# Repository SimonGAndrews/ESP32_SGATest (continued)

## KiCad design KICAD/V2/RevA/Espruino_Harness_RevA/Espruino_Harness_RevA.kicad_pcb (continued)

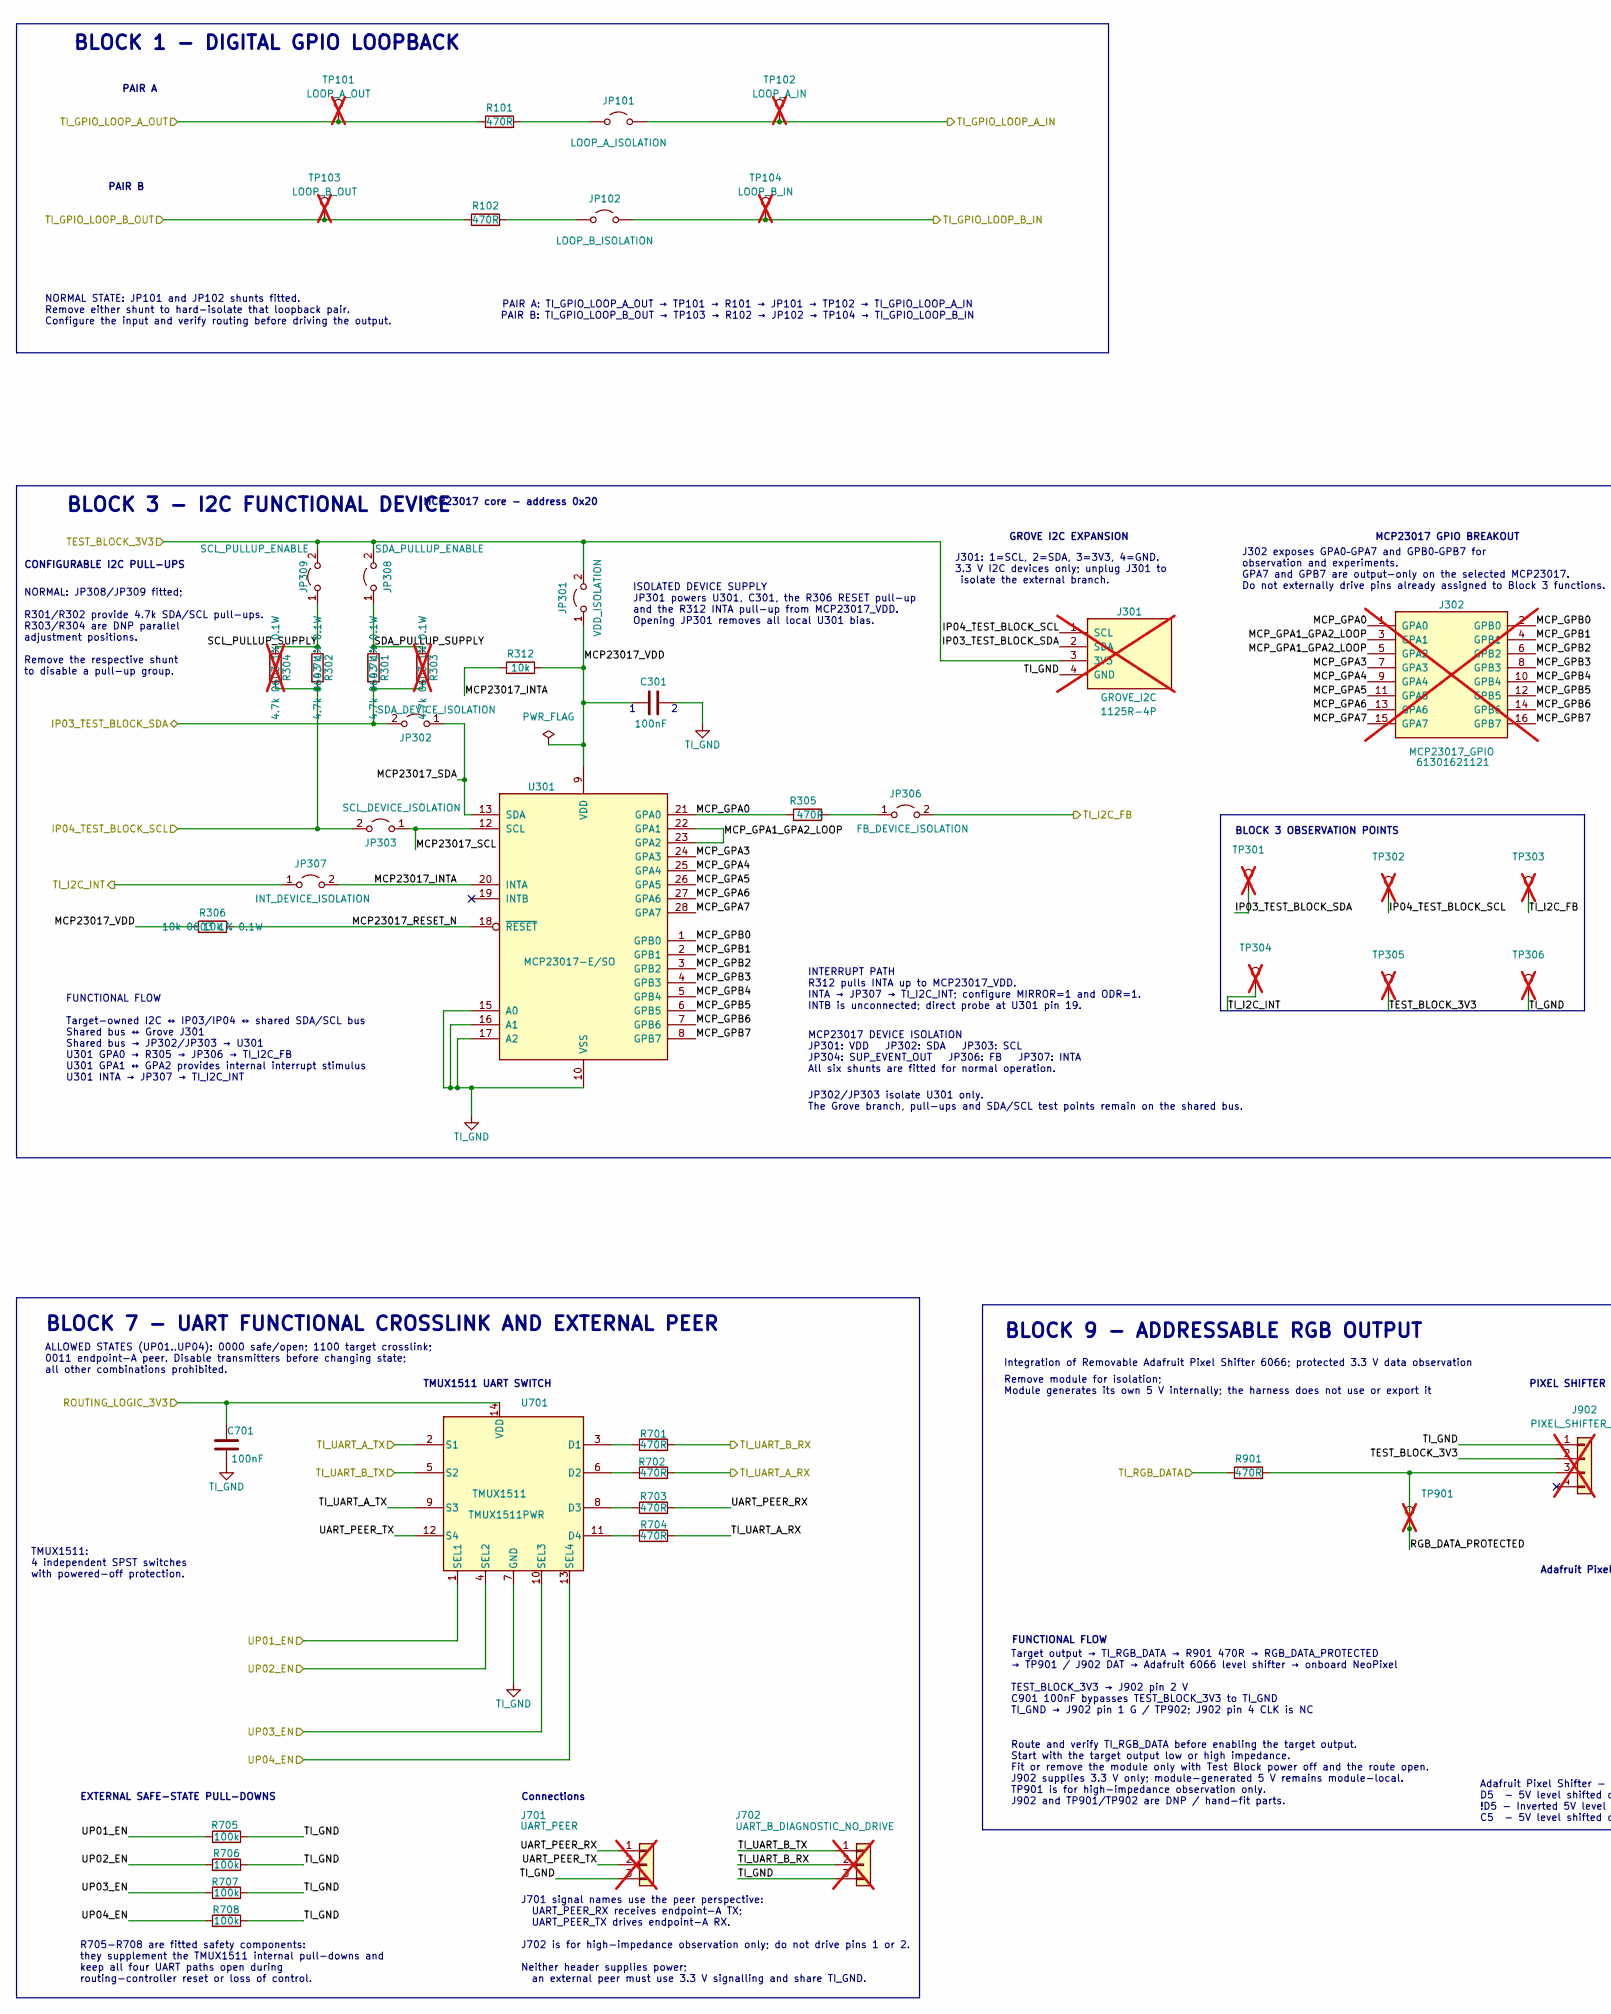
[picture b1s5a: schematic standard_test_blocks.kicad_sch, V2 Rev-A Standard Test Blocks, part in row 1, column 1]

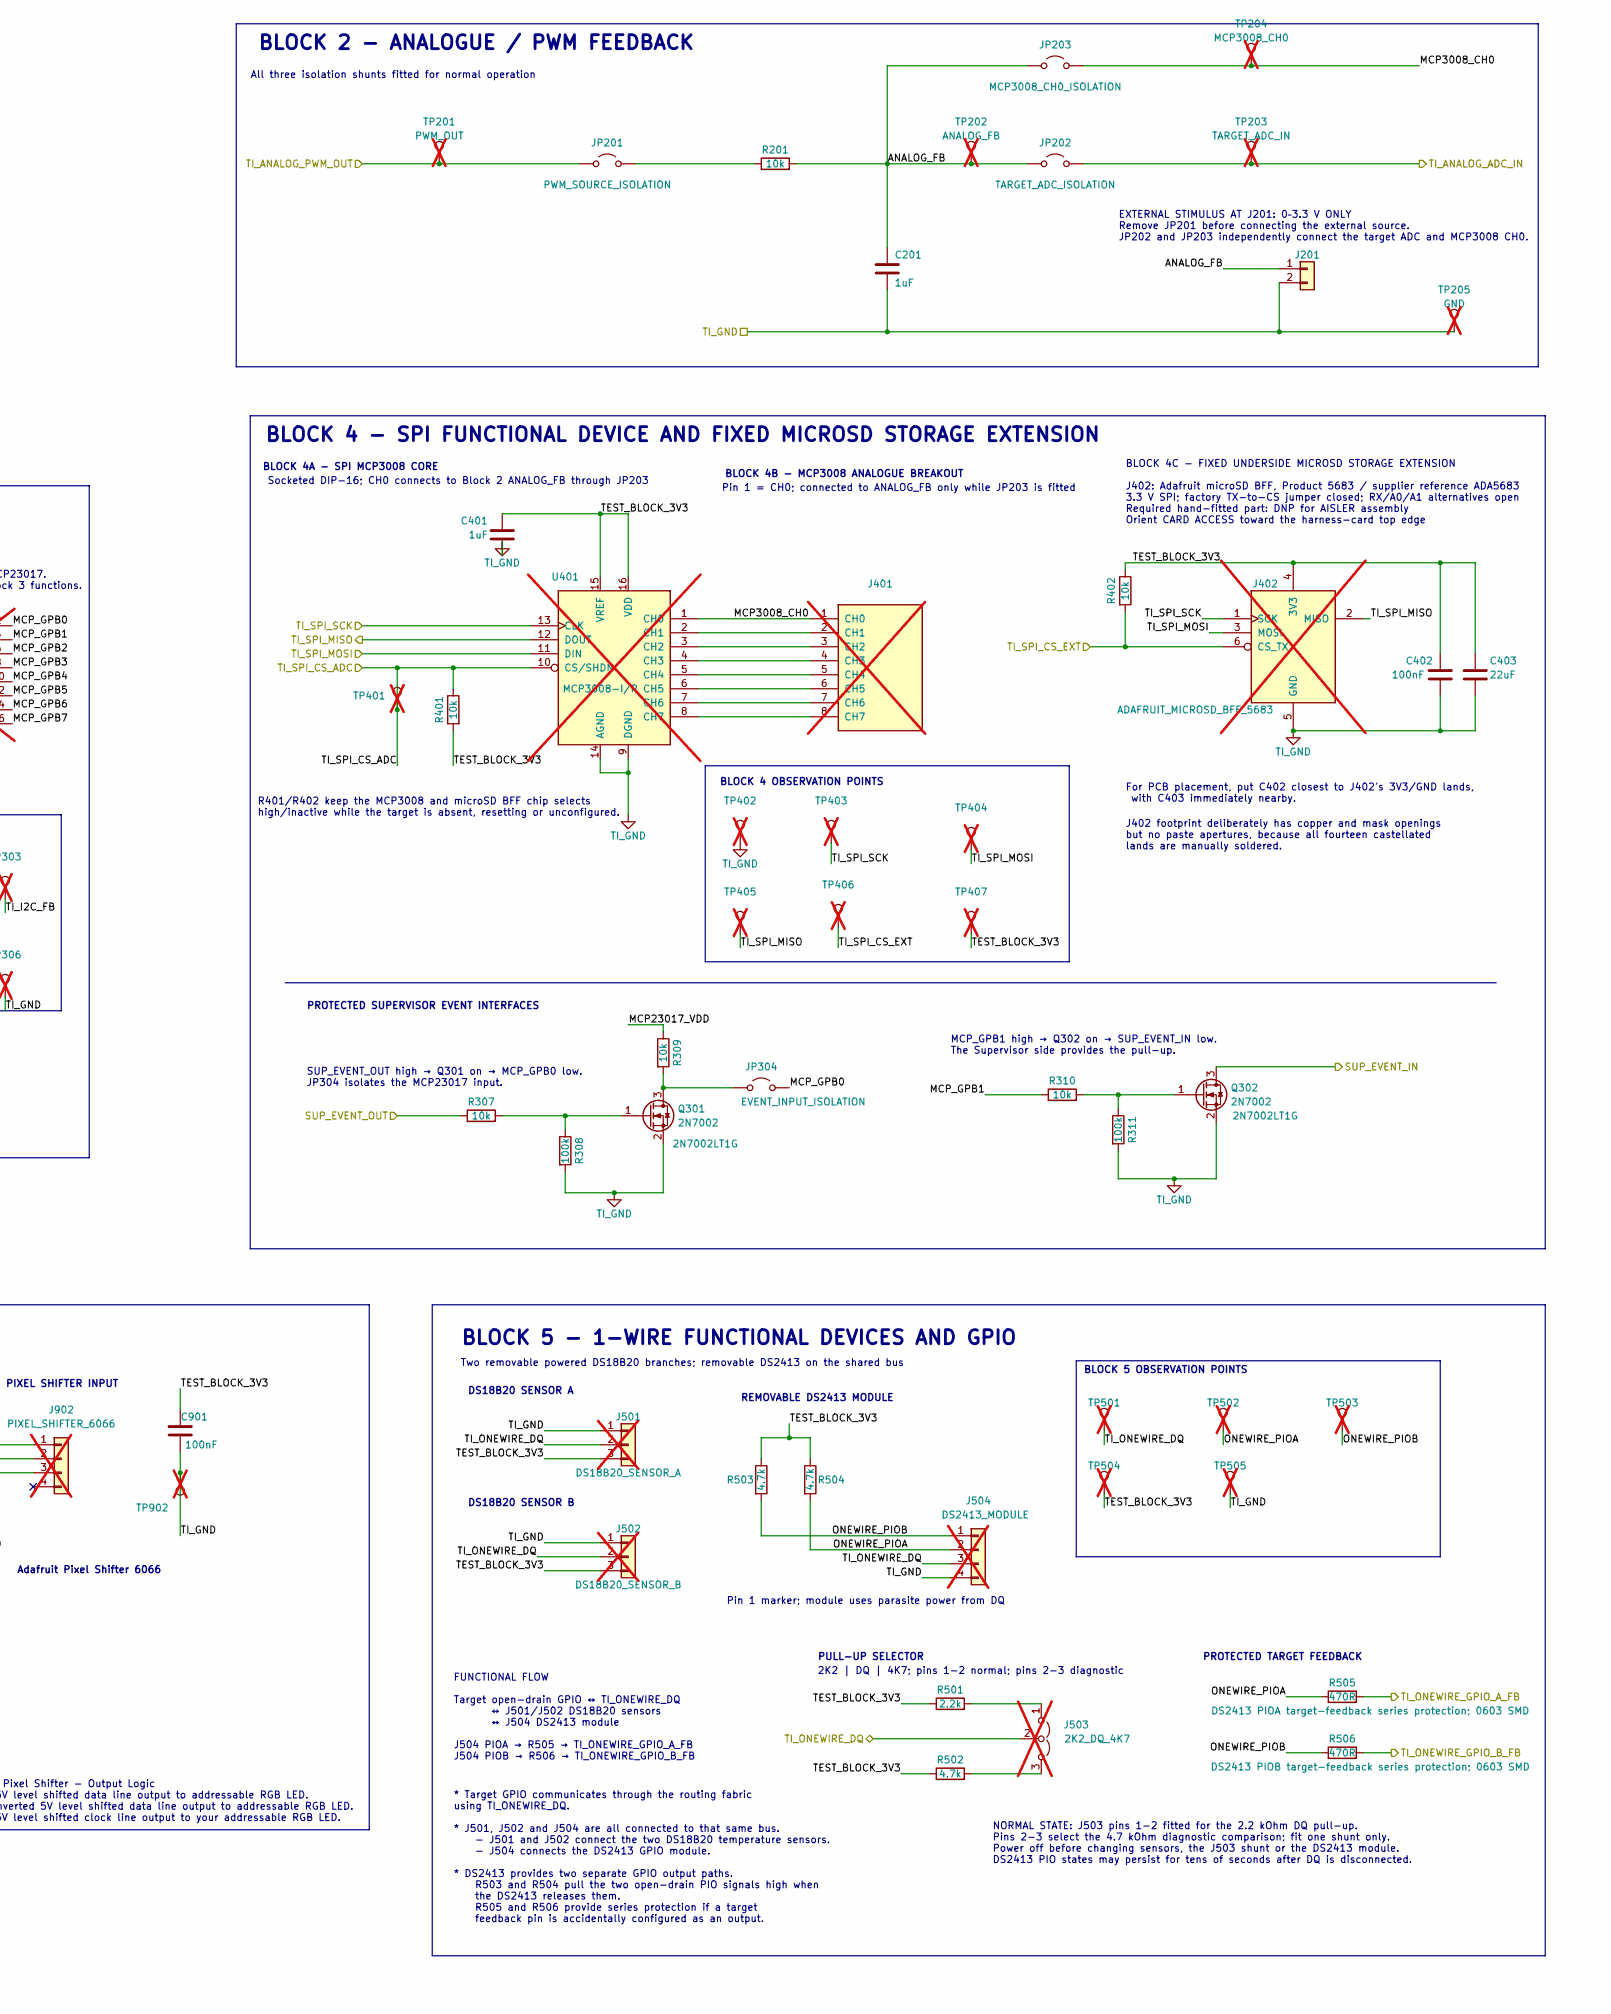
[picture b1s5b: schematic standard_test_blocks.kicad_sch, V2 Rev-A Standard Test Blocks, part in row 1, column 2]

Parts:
C201: 1uF; C_0603_1608Metric; MPN C1608X7R1C105K080AC
C301, C402, C701, C901: 100nF; C_0603_1608Metric
C401: 1uF; C_0603_1608Metric
C403: 22uF; C_0805_2012Metric
J201: EXTERNAL_ANALOG_STIMULUS_0_TO_3V3; PinHeader_1x02_P2.54mm_Vertical; MPN 61300211121
J301: GROVE_I2C; Grove_1x04_P2mm_RightAngle_Seeed_320110034; MPN 1125R-4P; not fitted
J302: MCP23017_GPIO; PinHeader_2x08_P2.54mm_Vertical; MPN 61301621121; not fitted
J401: MCP3008_ANALOGUE_BREAKOUT; PinHeader_1x08_P2.54mm_Vertical; MPN 61300811121; not fitted
J402: ADAFRUIT_MICROSD_BFF_5683; Adafruit_MicroSD_BFF_5683_Underside; MPN 5683; not fitted
J501: DS18B20_SENSOR_A; TerminalBlock_Phoenix_MPT-0,5-3-2.54_1x03_P2.54mm_Horizontal; MPN 1725669; not fitted
J502: DS18B20_SENSOR_B; TerminalBlock_Phoenix_MPT-0,5-3-2.54_1x03_P2.54mm_Horizontal; MPN 1725669; not fitted
J503: 2K2_DQ_4K7; PinHeader_1x03_P2.54mm_Vertical; MPN 61300311121; not fitted
J504: DS2413_MODULE; PinHeader_1x04_P2.54mm_Vertical; MPN 61300411121; not fitted
J701: UART_PEER; PinHeader_1x03_P2.54mm_Vertical; MPN 61300311121; not fitted
J702: UART_B_DIAGNOSTIC_NO_DRIVE; PinHeader_1x03_P2.54mm_Vertical; MPN 61300311121; not fitted
J902: PIXEL_SHIFTER_6066; PinHeader_1x04_P2.54mm_Horizontal; MPN 61300411021; not fitted
JP101: LOOP_A_ISOLATION; PinHeader_1x02_P2.54mm_Vertical; MPN 61300211121
JP102: LOOP_B_ISOLATION; PinHeader_1x02_P2.54mm_Vertical; MPN 61300211121
JP201: PWM_SOURCE_ISOLATION; PinHeader_1x02_P2.54mm_Vertical; MPN 61300211121
JP202: TARGET_ADC_ISOLATION; PinHeader_1x02_P2.54mm_Vertical; MPN 61300211121
JP203: MCP3008_CH0_ISOLATION; PinHeader_1x02_P2.54mm_Vertical; MPN 61300211121
JP301: VDD_ISOLATION; PinHeader_1x02_P2.54mm_Vertical; MPN 61300211121
JP302: SDA_DEVICE_ISOLATION; PinHeader_1x02_P2.54mm_Vertical; MPN 61300211121
JP303: SCL_DEVICE_ISOLATION; PinHeader_1x02_P2.54mm_Vertical; MPN 61300211121
JP304: EVENT_INPUT_ISOLATION; PinHeader_1x02_P2.54mm_Vertical; MPN 61300211121
JP306: FB_DEVICE_ISOLATION; PinHeader_1x02_P2.54mm_Vertical; MPN 61300211121
JP307: INT_DEVICE_ISOLATION; PinHeader_1x02_P2.54mm_Vertical; MPN 61300211121
JP308: SDA_PULLUP_ENABLE; PinHeader_1x02_P2.54mm_Vertical; MPN 61300211121
JP309: SCL_PULLUP_ENABLE; PinHeader_1x02_P2.54mm_Vertical; MPN 61300211121
Q301, Q302: 2N7002; SOT-23; MPN 2N7002LT1G
R101, R102: 470R; R_0603_1608Metric; MPN RC0603FR-07470RL
R201: 10k; R_0603_1608Metric; MPN RC0603FR-0710KL
R301, R302, R502, R503, R504: 4.7k; R_0603_1608Metric
R303, R304: 4.7k DNP; R_0603_1608Metric; not fitted
R305, R505, R506, R701, R702, R703, R704, R901: 470R; R_0603_1608Metric
R306, R307, R309, R310, R312, R401, R402: 10k; R_0603_1608Metric
R308, R311, R705, R706, R707, R708: 100k; R_0603_1608Metric
R501: 2.2k; R_0603_1608Metric
TP101: LOOP_A_OUT; PinHeader_1x01_P2.54mm_Vertical; MPN 61300111121; not fitted
TP102: LOOP_A_IN; PinHeader_1x01_P2.54mm_Vertical; MPN 61300111121; not fitted
TP103: LOOP_B_OUT; PinHeader_1x01_P2.54mm_Vertical; MPN 61300111121; not fitted
TP104: LOOP_B_IN; PinHeader_1x01_P2.54mm_Vertical; MPN 61300111121; not fitted
TP201: PWM_OUT; PinHeader_1x01_P2.54mm_Vertical; MPN 61300111121; not fitted
TP202: ANALOG_FB; PinHeader_1x01_P2.54mm_Vertical; MPN 61300111121; not fitted
TP203: TARGET_ADC_IN; PinHeader_1x01_P2.54mm_Vertical; MPN 61300111121; not fitted
TP204: MCP3008_CH0; PinHeader_1x01_P2.54mm_Vertical; MPN 61300111121; not fitted
TP205, TP306, TP402, TP505: GND; PinHeader_1x01_P2.54mm_Vertical; MPN 61300111121; not fitted
TP301: SDA; PinHeader_1x01_P2.54mm_Vertical; MPN 61300111121; not fitted
TP302: SCL; PinHeader_1x01_P2.54mm_Vertical; MPN 61300111121; not fitted
TP303: TI_I2C_FB; PinHeader_1x01_P2.54mm_Vertical; MPN 61300111121; not fitted
TP304: TI_I2C_INT; PinHeader_1x01_P2.54mm_Vertical; MPN 61300111121; not fitted
TP305, TP504: 3V3; PinHeader_1x01_P2.54mm_Vertical; MPN 61300111121; not fitted
TP401: TI_SPI_CS_ADC; PinHeader_1x01_P2.54mm_Vertical; MPN 61300111121; not fitted
TP403: TI_SPI_SCK; PinHeader_1x01_P2.54mm_Vertical; MPN 61300111121; not fitted
TP404: TI_SPI_MOSI; PinHeader_1x01_P2.54mm_Vertical; MPN 61300111121; not fitted
TP405: TI_SPI_MISO; PinHeader_1x01_P2.54mm_Vertical; MPN 61300111121; not fitted
TP406: TI_SPI_CS_EXT; PinHeader_1x01_P2.54mm_Vertical; MPN 61300111121; not fitted
TP407: TEST_BLOCK_3V3; PinHeader_1x01_P2.54mm_Vertical; MPN 61300111121; not fitted
TP501: ONEWIRE_DQ; PinHeader_1x01_P2.54mm_Vertical; MPN 61300111121; not fitted
TP502: ONEWIRE_PIOA; PinHeader_1x01_P2.54mm_Vertical; MPN 61300111121; not fitted
TP503: ONEWIRE_PIOB; PinHeader_1x01_P2.54mm_Vertical; MPN 61300111121; not fitted
TP901: RGB_DATA_PROTECTED; PinHeader_1x01_P2.54mm_Vertical; MPN 61300111121; not fitted
TP902: RGB_GND; PinHeader_1x01_P2.54mm_Vertical; MPN 61300111121; not fitted
U301: MCP23017-E/SO; SOIC-28W_7.5x17.9mm_P1.27mm; MPN MCP23017-E/SO
U401: MCP3008; DIP-16_W7.62mm_LongPads; MPN MCP3008-I/P; not fitted
U701: TMUX1511; TSSOP-14_4.4x5mm_P0.65mm; MPN TMUX1511PWR

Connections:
/IP03_TEST_BLOCK_SDA: J301.2 (SDA), JP302.2 (B), R301.2, R303.2, TP301.1; also elsewhere on the board
/IP04_TEST_BLOCK_SCL: J301.1 (SCL), JP303.2 (B), R302.2, R304.2, TP302.1; also elsewhere on the board
/ROUTING_LOGIC_3V3: C701.1, U701.14 (VDD); also elsewhere on the board
/SUP_EVENT_IN: Q302.3 (D); also elsewhere on the board
/SUP_EVENT_OUT: R307.1; also elsewhere on the board
/Standard_Test_Blocks/ANALOG_FB: C201.1, J201.1, JP202.1 (A), JP203.1 (A), R201.2, TP202.1
/Standard_Test_Blocks/MCP3008_CH0: J401.1 (CH0), JP203.2 (B), TP204.1, U401.1 (CH0)
/Standard_Test_Blocks/MCP23017_INTA: JP307.2 (B), R312.1, U301.20 (INTA)
/Standard_Test_Blocks/MCP23017_RESET_N: R306.1, U301.18 (~RESET)
/Standard_Test_Blocks/MCP23017_SCL: JP303.1 (A), U301.12 (SCL)
/Standard_Test_Blocks/MCP23017_SDA: JP302.1 (A), U301.13 (SDA)
/Standard_Test_Blocks/MCP23017_VDD: C301.1, JP301.1 (A), R306.2, R309.1, R312.2, U301.9 (VDD)
/Standard_Test_Blocks/MCP_GPA0: J302.1 (GPA0), R305.1, U301.21 (GPA0)
/Standard_Test_Blocks/MCP_GPA1_GPA2_LOOP: J302.3 (GPA1), J302.5 (GPA2), U301.22 (GPA1), U301.23 (GPA2)
/Standard_Test_Blocks/MCP_GPA3: J302.7 (GPA3), U301.24 (GPA3)
/Standard_Test_Blocks/MCP_GPA4: J302.9 (GPA4), U301.25 (GPA4)
/Standard_Test_Blocks/MCP_GPA5: J302.11 (GPA5), U301.26 (GPA5)
/Standard_Test_Blocks/MCP_GPA6: J302.13 (GPA6), U301.27 (GPA6)
/Standard_Test_Blocks/MCP_GPA7: J302.15 (GPA7), U301.28 (GPA7)
/Standard_Test_Blocks/MCP_GPB0: J302.2 (GPB0), JP304.2 (B), U301.1 (GPB0)
/Standard_Test_Blocks/MCP_GPB1: J302.4 (GPB1), R310.1, U301.2 (GPB1)
/Standard_Test_Blocks/MCP_GPB2: J302.6 (GPB2), U301.3 (GPB2)
/Standard_Test_Blocks/MCP_GPB3: J302.8 (GPB3), U301.4 (GPB3)
/Standard_Test_Blocks/MCP_GPB4: J302.10 (GPB4), U301.5 (GPB4)
/Standard_Test_Blocks/MCP_GPB5: J302.12 (GPB5), U301.6 (GPB5)
/Standard_Test_Blocks/MCP_GPB6: J302.14 (GPB6), U301.7 (GPB6)
/Standard_Test_Blocks/MCP_GPB7: J302.16 (GPB7), U301.8 (GPB7)
/Standard_Test_Blocks/ONEWIRE_PIOA: J504.2, R504.2, R505.1, TP502.1
/Standard_Test_Blocks/ONEWIRE_PIOB: J504.1, R503.2, R506.1, TP503.1
/Standard_Test_Blocks/RGB_DATA_PROTECTED: J902.3, R901.2, TP901.1
/Standard_Test_Blocks/SCL_PULLUP_SUPPLY: JP309.1 (A), R302.1, R304.1
/Standard_Test_Blocks/SDA_PULLUP_SUPPLY: JP308.1 (A), R301.1, R303.1
/Standard_Test_Blocks/UART_PEER_RX: J701.1, R703.2
/Standard_Test_Blocks/UART_PEER_TX: J701.2, U701.12 (S4)
/TEST_BLOCK_3V3: C401.1, C402.1, C403.1, C901.1, J301.3 (3V3), J402.4 (3V3), J501.3, J502.3, J902.2, JP301.2 (B), JP308.2 (B), JP309.2 (B), R401.2, R402.1, R501.1, R502.1, R503.1, R504.1, TP305.1, TP407.1, TP504.1, U401.15 (VREF), U401.16 (VDD); also elsewhere on the board
/TI_ANALOG_ADC_IN: JP202.2 (B), TP203.1; also elsewhere on the board
/TI_ANALOG_PWM_OUT: JP201.1 (A), TP201.1; also elsewhere on the board
/TI_GPIO_LOOP_A_IN: JP101.2 (B), TP102.1; also elsewhere on the board
/TI_GPIO_LOOP_A_OUT: R101.1, TP101.1; also elsewhere on the board
/TI_GPIO_LOOP_B_IN: JP102.2 (B), TP104.1; also elsewhere on the board
/TI_GPIO_LOOP_B_OUT: R102.1, TP103.1; also elsewhere on the board
/TI_I2C_FB: JP306.2 (B), TP303.1; also elsewhere on the board
/TI_I2C_INT: JP307.1 (A), TP304.1; also elsewhere on the board
/TI_ONEWIRE_DQ: J501.2, J502.2, J503.2 (C), J504.3, TP501.1; also elsewhere on the board
/TI_ONEWIRE_GPIO_A_FB: R505.2; also elsewhere on the board
/TI_ONEWIRE_GPIO_B_FB: R506.2; also elsewhere on the board
/TI_RGB_DATA: R901.1; also elsewhere on the board
/TI_SPI_CS_ADC: R401.1, TP401.1, U401.10 (CS/SHDN); also elsewhere on the board
/TI_SPI_CS_EXT: J402.6 (CS_TX), R402.2, TP406.1; also elsewhere on the board
/TI_SPI_MISO: J402.2 (MISO), TP405.1, U401.12 (DOUT); also elsewhere on the board
/TI_SPI_MOSI: J402.3 (MOSI), TP404.1, U401.11 (DIN); also elsewhere on the board
/TI_SPI_SCK: J402.1 (SCK), TP403.1, U401.13 (CLK); also elsewhere on the board
/TI_UART_A_RX: R702.2, R704.2; also elsewhere on the board
/TI_UART_A_TX: U701.2 (S1), U701.9 (S3); also elsewhere on the board
/TI_UART_B_RX: J702.2, R701.2; also elsewhere on the board
/TI_UART_B_TX: J702.1, U701.5 (S2); also elsewhere on the board
/UP01_EN: R705.1, U701.1 (SEL1); also elsewhere on the board
/UP02_EN: R706.1, U701.4 (SEL2); also elsewhere on the board
/UP03_EN: R707.1, U701.10 (SEL3); also elsewhere on the board
/UP04_EN: R708.1, U701.13 (SEL4); also elsewhere on the board
unnamed: J401.2 (CH1), U401.2 (CH1)
unnamed: J401.3 (CH2), U401.3 (CH2)
unnamed: J401.4 (CH3), U401.4 (CH3)
unnamed: J401.5 (CH4), U401.5 (CH4)
unnamed: J401.6 (CH5), U401.6 (CH5)
unnamed: J401.7 (CH6), U401.7 (CH6)
unnamed: J401.8 (CH7), U401.8 (CH7)
unnamed: J503.1 (A), R501.2
unnamed: J503.3 (B), R502.2
unnamed: JP101.1 (A), R101.2
unnamed: JP102.1 (A), R102.2
unnamed: JP201.2 (B), R201.1
unnamed: JP304.1 (A), Q301.3 (D), R309.2
unnamed: JP306.1 (A), R305.2
unnamed: Q301.1 (G), R307.2, R308.1
unnamed: Q302.1 (G), R310.2, R311.1
unnamed: R701.1, U701.3 (D1)
unnamed: R702.1, U701.6 (D2)
unnamed: R703.1, U701.8 (D3)
unnamed: R704.1, U701.11 (D4)
TI_GND: C201.2, C301.2, C401.2, C402.2, C403.2, C701.2, C901.2, J201.2, J301.4 (GND), J402.5 (GND), J501.1, J502.1, J504.4, J701.3, J702.3, J902.1, Q301.2 (S), Q302.2 (S), R308.2, R311.2, R705.2, R706.2, R707.2, R708.2, TP205.1, TP306.1, TP402.1, TP505.1, TP902.1, U301.10 (VSS), U301.15 (A0), U301.16 (A1), U301.17 (A2), U401.9 (DGND), U401.14 (AGND), U701.7 (GND); also elsewhere on the board

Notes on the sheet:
Route and verify TI_RGB_DATA before enabling the target output. Start with the target output low or high impedance. Fit or remove the module only with Test Block power off and the route open. J902 supplies 3.3 V only; module-generated 5 V remains module-local. TP901 is for high-impedance observatio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
BLOCK 3 OBSERVATION POINTS
FUNCTIONAL FLOW Target open-drain GPIO ↔ TI_ONEWIRE_DQ ↔ J501/J502 DS18B20 sensors ↔ J504 DS2413 module J504 PIOA → R505 → TI_ONEWIRE_GPIO_A_FB J504 PIOB → R506 → TI_ONEWIRE_GPIO_B_FB
J302 exposes GPA0–GPA7 and GPB0–GPB7 for observation and experiments. GPA7 and GPB7 are output-only on the selected MCP23017. Do not externally drive pins already assigned to Block 3 functions.
PAIR A
BLOCK 4C - FIXED UNDERSIDE MICROSD STORAGE EXTENSION J402: Adafruit microSD BFF, Product 5683 / supplier reference ADA5683 3.3 V SPI; factory TX-to-CS jumper closed; RX/A0/A1 alternatives open Required hand-fitted part: DNP for AISLER assembly Orient CARD ACCESS toward the harness-card top edge
TMUX1511: 4 independent SPST switches with powered-off protection.
MCP23017 DEVICE ISOLATION JP301: VDD JP302: SDA JP303: SCL JP304: SUP_EVENT_OUT JP306: FB JP307: INTA All six shunts are fitted for normal operation.
NORMAL: JP308/JP309 fitted; R301/R302 provide 4.7k SDA/SCL pull-ups. R303/R304 are DNP parallel adjustment positions. Remove the respective shunt to disable a pull-up group.
All three isolation shunts fitted for normal operation
BLOCK 4 - SPI FUNCTIONAL DEVICE AND FIXED MICROSD STORAGE EXTENSION
BLOCK 4A - SPI MCP3008 CORE
MCP23017 GPIO BREAKOUT
FUNCTIONAL FLOW
* Target GPIO communicates through the routing fabric using TI_ONEWIRE_DQ. * J501, J502 and J504 are all connected to that same bus. - J501 and J502 connect the two DS18B20 temperature sensors. - J504 connects the DS2413 GPIO module. * DS2413 provides two separate GPIO output paths. R503 and R504 p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
EXTERNAL STIMULUS AT J201: 0–3.3 V ONLY Remove JP201 before connecting the external source. JP202 and JP203 independently connect the target ADC and MCP3008 CH0.
CONFIGURABLE I2C PULL-UPS
ISOLATED DEVICE SUPPLY JP301 powers U301, C301, the R306 RESET pull-up and the R312 INTA pull-up from MCP23017_VDD. Opening JP301 removes all local U301 bias.
BLOCK 2 - ANALOGUE / PWM FEEDBACK
BLOCK 4B - MCP3008 ANALOGUE BREAKOUT
SUP_EVENT_OUT high → Q301 on → MCP_GPB0 low. JP304 isolates the MCP23017 input.
PAIR B
JP302/JP303 isolate U301 only. The Grove branch, pull-ups and SDA/SCL test points remain on the shared bus.
FUNCTIONAL FLOW Target-owned I2C ↔ IP03/IP04 ↔ shared SDA/SCL bus Shared bus ↔ Grove J301 Shared bus → JP302/JP303 → U301 U301 GPA0 → R305 → JP306 → TI_I2C_FB U301 GPA1 ↔ GPA2 provides internal interrupt stimulus U301 INTA → JP307 → TI_I2C_INT
BLOCK 4 OBSERVATION POINTS
NORMAL STATE: JP101 and JP102 shunts fitted. Remove either shunt to hard-isolate that loopback pair. Configure the input and verify routing before driving the output.
Adafruit Pixel Shifter - Output Logic D5 - 5V level shifted data line output to addressable RGB LED. !D5 - Inverted 5V level shifted data line output to addressable RGB LED. C5 - 5V level shifted clock line output to your addressable RGB LED.
J402 footprint deliberately has copper and mask openings but no paste apertures, because all fourteen castellated lands are manually soldered.
Socketed DIP-16; CH0 connects to Block 2 ANALOG_FB through JP203
Pin 1 = CH0; connected to ANALOG_FB only while JP203 is fitted
GROVE I2C EXPANSION
Adafruit Pixel Shifter 6066
R401/R402 keep the MCP3008 and microSD BFF chip selects high/inactive while the target is absent, resetting or unconfigured.
BLOCK 5 - 1-WIRE FUNCTIONAL DEVICES AND GPIO
Two removable powered DS18B20 branches; removable DS2413 on the shared bus
DS18B20 SENSOR A
DS18B20 SENSOR B
PULL-UP SELECTOR
2K2 | DQ | 4K7; pins 1-2 normal; pins 2-3 diagnostic
REMOVABLE DS2413 MODULE

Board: 2 copper layers, 232 parts (1 on the bottom side), 162 nets, no tracks yet.

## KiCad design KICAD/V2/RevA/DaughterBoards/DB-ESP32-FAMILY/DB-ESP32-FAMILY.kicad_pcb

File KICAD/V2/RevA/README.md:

# V2 Rev-A Project

The fresh Rev-A KiCad project is located at:

```text
KICAD/V2/RevA/Espruino_Harness_RevA/
```

It was created through KiCad as a new project rather than copied from the
exploratory schematic or PCB. Bring across only individually reviewed symbols,
footprints and implementation decisions, keeping each accepted library local
to the Rev-A project and referenced through `${KIPRJMOD}`.

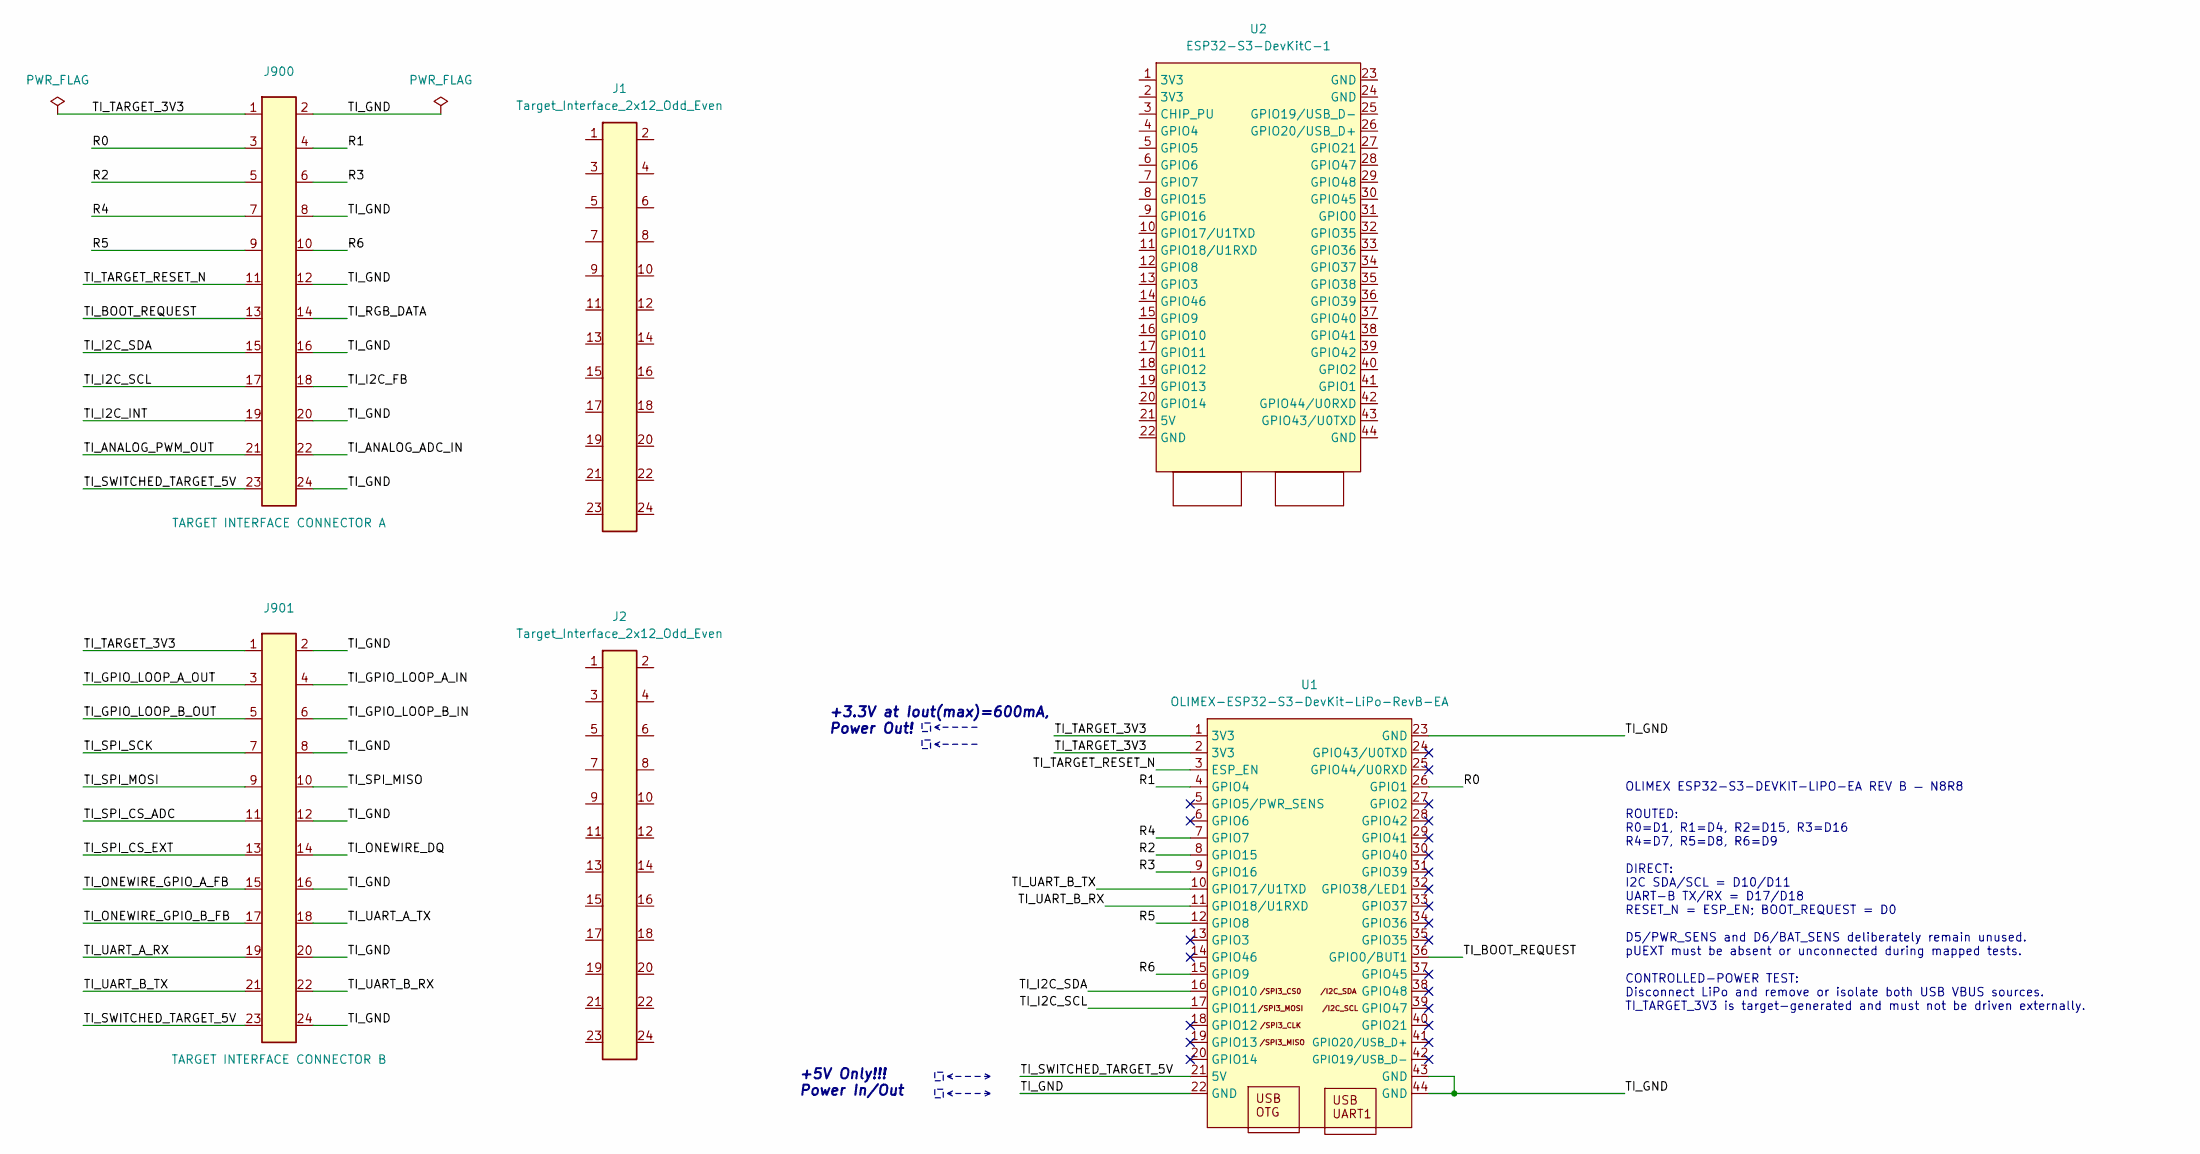
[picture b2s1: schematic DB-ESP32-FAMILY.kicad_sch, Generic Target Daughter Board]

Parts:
J1, J2: Target_Interface_2x12_Odd_Even; TargetInterface_2x12_P2.54mm_RA_Male_Adafruit1541_Daughter
J900: TARGET INTERFACE CONNECTOR A; TargetInterface_2x12_P2.54mm_RA_Male_Adafruit1541_Daughter
J901: TARGET INTERFACE CONNECTOR B; TargetInterface_2x12_P2.54mm_RA_Male_Adafruit1541_Daughter
U1: OLIMEX-ESP32-S3-DevKit-LiPo-RevB-EA; OLIMEX-ESP32-S3-DevKit-LiPo-EA
U2: ESP32-S3-DevKitC-1

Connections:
/R0: J900.3 (Contact_03), U1.26 (GPIO1)
/R1: J900.4 (Contact_04), U1.4 (GPIO4)
/R2: J900.5 (Contact_05), U1.8 (GPIO15)
/R3: J900.6 (Contact_06), U1.9 (GPIO16)
/R4: J900.7 (Contact_07), U1.7 (GPIO7)
/R5: J900.9 (Contact_09), U1.12 (GPIO8)
/R6: J900.10 (Contact_10), U1.15 (GPIO9)
/TI_ANALOG_ADC_IN: J900.22 (Contact_22)
/TI_ANALOG_PWM_OUT: J900.21 (Contact_21)
/TI_BOOT_REQUEST: J900.13 (Contact_13), U1.36 (GPIO0/BUT1)
/TI_GND: J900.2 (Contact_02), J900.8 (Contact_08), J900.12 (Contact_12), J900.16 (Contact_16), J900.20 (Contact_20), J900.24 (Contact_24), J901.2 (Contact_02), J901.8 (Contact_08), J901.12 (Contact_12), J901.16 (Contact_16), J901.20 (Contact_20), J901.24 (Contact_24), U1.22 (GND), U1.23 (GND), U1.43 (GND), U1.44 (GND)
/TI_GPIO_LOOP_A_IN: J901.4 (Contact_04)
/TI_GPIO_LOOP_A_OUT: J901.3 (Contact_03)
/TI_GPIO_LOOP_B_IN: J901.6 (Contact_06)
/TI_GPIO_LOOP_B_OUT: J901.5 (Contact_05)
/TI_I2C_FB: J900.18 (Contact_18)
/TI_I2C_INT: J900.19 (Contact_19)
/TI_I2C_SCL: J900.17 (Contact_17), U1.17 (GPIO11)
/TI_I2C_SDA: J900.15 (Contact_15), U1.16 (GPIO10)
/TI_ONEWIRE_DQ: J901.14 (Contact_14)
/TI_ONEWIRE_GPIO_A_FB: J901.15 (Contact_15)
/TI_ONEWIRE_GPIO_B_FB: J901.17 (Contact_17)
/TI_RGB_DATA: J900.14 (Contact_14)
/TI_SPI_CS_ADC: J901.11 (Contact_11)
/TI_SPI_CS_EXT: J901.13 (Contact_13)
/TI_SPI_MISO: J901.10 (Contact_10)
/TI_SPI_MOSI: J901.9 (Contact_09)
/TI_SPI_SCK: J901.7 (Contact_07)
/TI_SWITCHED_TARGET_5V: J900.23 (Contact_23), J901.23 (Contact_23), U1.21 (5V)
/TI_TARGET_3V3: J900.1 (Contact_01), J901.1 (Contact_01), U1.1 (3V3), U1.2 (3V3)
/TI_TARGET_RESET_N: J900.11 (Contact_11), U1.3 (ESP_EN)
/TI_UART_A_RX: J901.19 (Contact_19)
/TI_UART_A_TX: J901.18 (Contact_18)
/TI_UART_B_RX: J901.22 (Contact_22), U1.11 (GPIO18/U1RXD)
/TI_UART_B_TX: J901.21 (Contact_21), U1.10 (GPIO17/U1TXD)

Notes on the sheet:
+3.3V at Iout(max)=600mA, Power Out!
OLIMEX ESP32-S3-DEVKIT-LIPO-EA REV B — N8R8 ROUTED: R0=D1, R1=D4, R2=D15, R3=D16 R4=D7, R5=D8, R6=D9 DIRECT: I2C SDA/SCL = D10/D11 UART-B TX/RX = D17/D18 RESET_N = ESP_EN; BOOT_REQUEST = D0 D5/PWR_SENS and D6/BAT_SENS deliberately remain unused. pUEXT must be absent or unconnected during mapped tes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
+5V Only!!! Power In/Out

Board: 2 copper layers, 6 parts (0 on the bottom side), 16 nets, no tracks yet.

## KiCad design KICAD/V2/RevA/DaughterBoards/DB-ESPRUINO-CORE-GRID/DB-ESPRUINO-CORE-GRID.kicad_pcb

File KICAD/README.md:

# KiCad Projects

All KiCad projects and component-development work live under this directory.
Libraries remain local to the project that uses them and use `${KIPRJMOD}` in
KiCad library tables.

## Directory map

```text
KICAD/
|-- V1/
|   |-- ESP32_C3_v1/       Completed ESP32-C3 V1 harness
|   `-- ESP32_V1/          Completed classic ESP32 V1 harness
`-- V2/
    |-- Exploration/
    |   `-- Espruino_Harness_V2/
    |-- ComponentDevelopment/
    |   `-- EspruinoPicoDirectMount/
    |-- RevA/
    `-- upstream/
```

`V2/Exploration/Espruino_Harness_V2/` preserves the earlier exploratory
schematic hierarchy, PCB placement work and curated target libraries. It is a
reference input to Rev A, not the Rev-A starting project.

`V2/ComponentDevelopment/EspruinoPicoDirectMount/` contains the useful
Espruino Pico direct-solder footprint and board-aperture development work. A
reviewed copy of the required footprint will be placed in the future Pico
daughter-board project's local library.

`V2/RevA/Espruino_Harness_RevA/` is the intended location for the fresh Rev-A
project. Create that project through KiCad rather than by copying the
exploratory schematic or PCB.

`V2/upstream/` contains local upstream source checkouts used for provenance and
comparison. It is ignored by Git and is not a production library.

KiCad local-state files, automatic backups, caches and lock files are ignored
by the repository-level `.gitignore`.

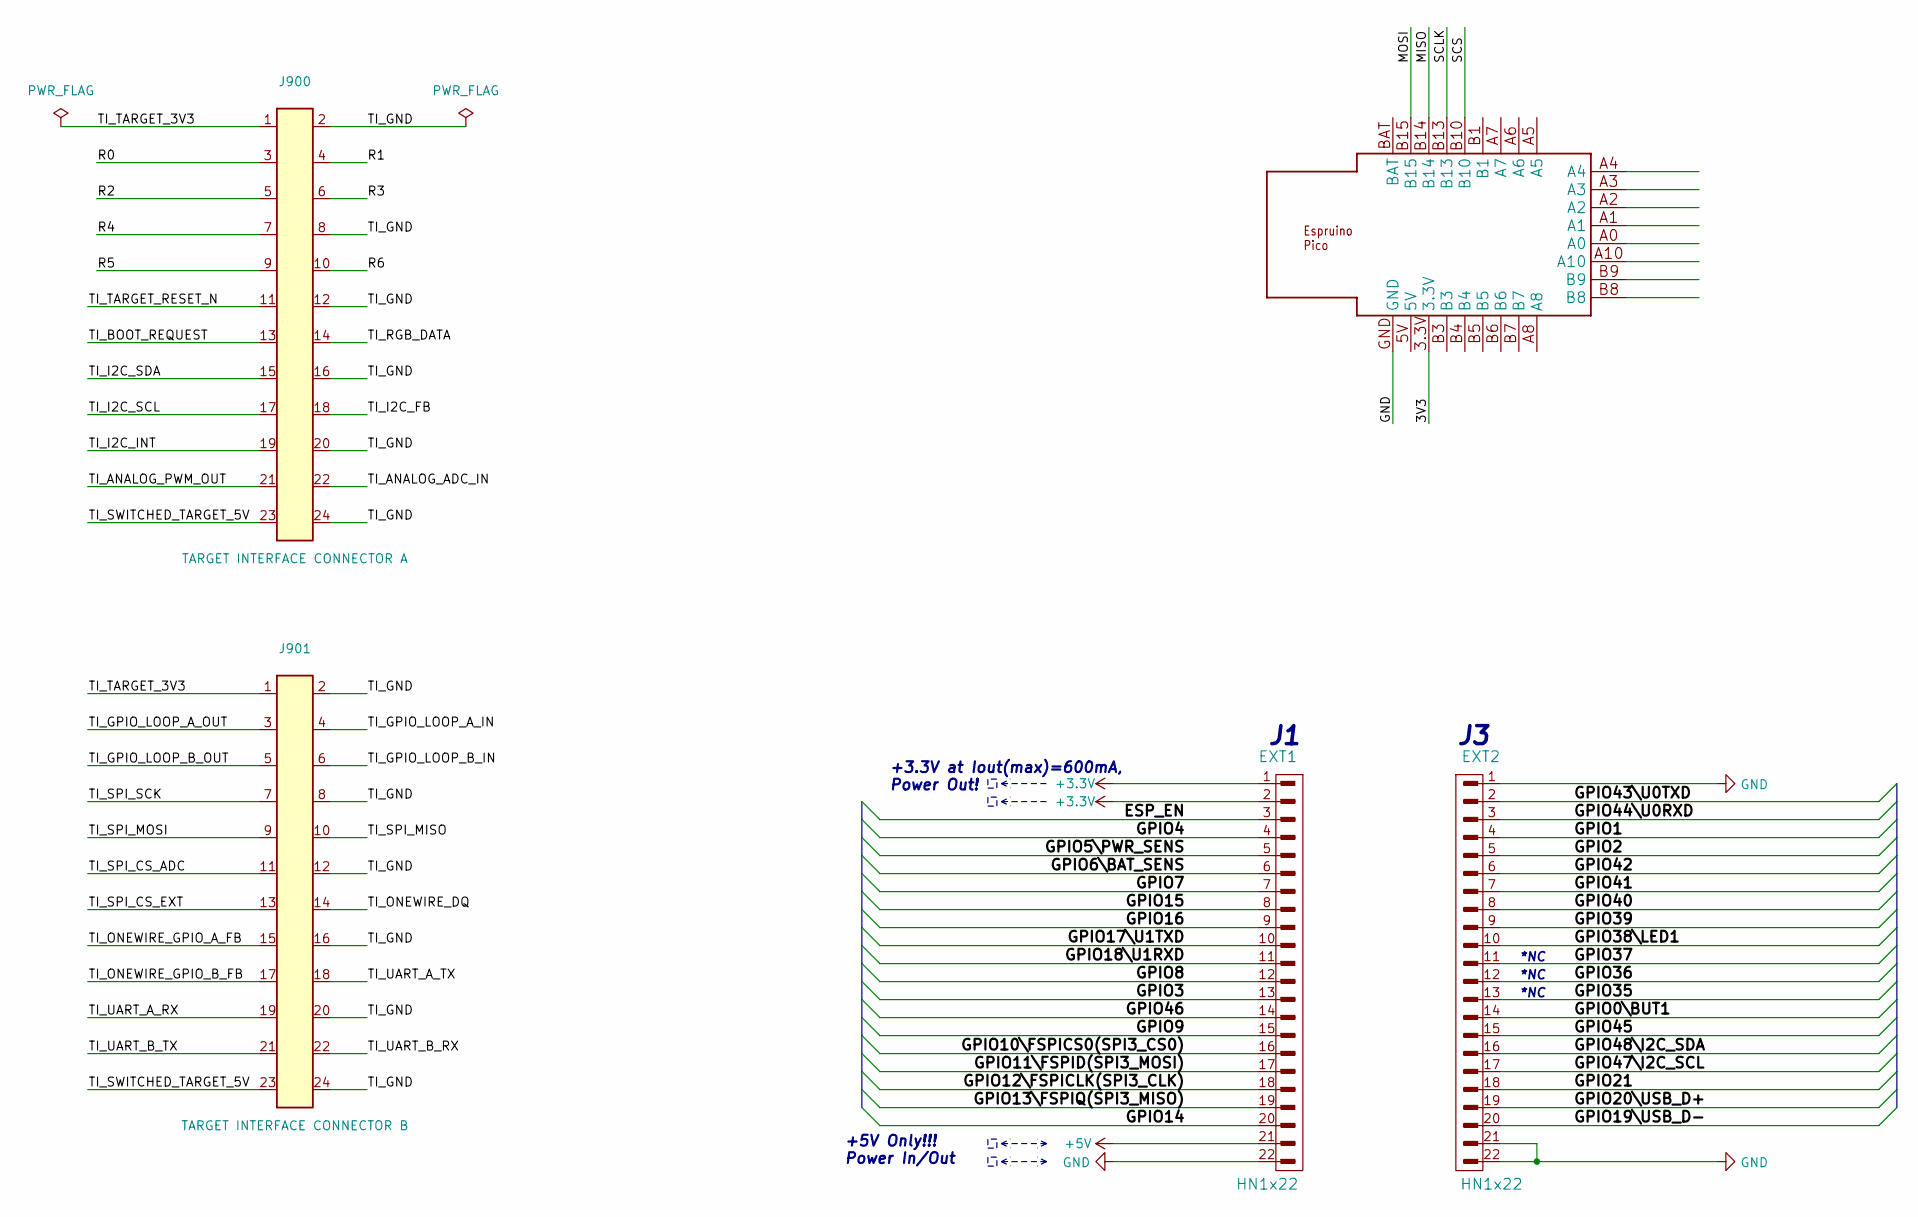
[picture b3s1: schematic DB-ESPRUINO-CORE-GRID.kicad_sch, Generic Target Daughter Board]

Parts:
EXT1, EXT2: HN1x22
J900: TARGET INTERFACE CONNECTOR A; TargetInterface_2x12_P2.54mm_RA_Male_Adafruit1541_Daughter
J901: TARGET INTERFACE CONNECTOR B; TargetInterface_2x12_P2.54mm_RA_Male_Adafruit1541_Daughter
U$1: ESPRUINO_PICO_SMD

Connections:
+3.3V: EXT1.1, EXT1.2
+5V: EXT1.21
/3V3: U$1.3.3V
/ESP_EN: EXT1.3
/GPIO0\BUT1: EXT2.14
/GPIO1: EXT2.4
/GPIO2: EXT2.5
/GPIO3: EXT1.13
/GPIO4: EXT1.4
/GPIO5\PWR_SENS: EXT1.5
/GPIO6\BAT_SENS: EXT1.6
/GPIO7: EXT1.7
/GPIO8: EXT1.12
/GPIO9: EXT1.15
/GPIO10\FSPICS0(SPI3_CS0): EXT1.16
/GPIO11\FSPID(SPI3_MOSI): EXT1.17
/GPIO12\FSPICLK(SPI3_CLK): EXT1.18
/GPIO13\FSPIQ(SPI3_MISO): EXT1.19
/GPIO14: EXT1.20
/GPIO15: EXT1.8
/GPIO16: EXT1.9
/GPIO17\U1TXD: EXT1.10
/GPIO18\U1RXD: EXT1.11
/GPIO19\USB_D-: EXT2.20
/GPIO20\USB_D+: EXT2.19
/GPIO21: EXT2.18
/GPIO35: EXT2.13
/GPIO36: EXT2.12
/GPIO37: EXT2.11
/GPIO38\LED1: EXT2.10
/GPIO39: EXT2.9
/GPIO40: EXT2.8
/GPIO41: EXT2.7
/GPIO42: EXT2.6
/GPIO43\U0TXD: EXT2.2
/GPIO44\U0RXD: EXT2.3
/GPIO45: EXT2.15
/GPIO46: EXT1.14
/GPIO47\I2C_SCL: EXT2.17
/GPIO48\I2C_SDA: EXT2.16
/MISO: U$1.B14
/MOSI: U$1.B15
/R0: J900.3 (Contact_03)
/R1: J900.4 (Contact_04)
/R2: J900.5 (Contact_05)
/R3: J900.6 (Contact_06)
/R4: J900.7 (Contact_07)
/R5: J900.9 (Contact_09)
/R6: J900.10 (Contact_10)
/SCLK: U$1.B13
/SCS: U$1.B10
/TI_ANALOG_ADC_IN: J900.22 (Contact_22)
/TI_ANALOG_PWM_OUT: J900.21 (Contact_21)
/TI_BOOT_REQUEST: J900.13 (Contact_13)
/TI_GND: J900.2 (Contact_02), J900.8 (Contact_08), J900.12 (Contact_12), J900.16 (Contact_16), J900.20 (Contact_20), J900.24 (Contact_24), J901.2 (Contact_02), J901.8 (Contact_08), J901.12 (Contact_12), J901.16 (Contact_16), J901.20 (Contact_20), J901.24 (Contact_24)
/TI_GPIO_LOOP_A_IN: J901.4 (Contact_04)
/TI_GPIO_LOOP_A_OUT: J901.3 (Contact_03)
/TI_GPIO_LOOP_B_IN: J901.6 (Contact_06)
/TI_GPIO_LOOP_B_OUT: J901.5 (Contact_05)
/TI_I2C_FB: J900.18 (Contact_18)
/TI_I2C_INT: J900.19 (Contact_19)
/TI_I2C_SCL: J900.17 (Contact_17)
/TI_I2C_SDA: J900.15 (Contact_15)
/TI_ONEWIRE_DQ: J901.14 (Contact_14)
/TI_ONEWIRE_GPIO_A_FB: J901.15 (Contact_15)
/TI_ONEWIRE_GPIO_B_FB: J901.17 (Contact_17)
/TI_RGB_DATA: J900.14 (Contact_14)
/TI_SPI_CS_ADC: J901.11 (Contact_11)
/TI_SPI_CS_EXT: J901.13 (Contact_13)
/TI_SPI_MISO: J901.10 (Contact_10)
/TI_SPI_MOSI: J901.9 (Contact_09)
/TI_SPI_SCK: J901.7 (Contact_07)
/TI_SWITCHED_TARGET_5V: J900.23 (Contact_23), J901.23 (Contact_23)
/TI_TARGET_3V3: J900.1 (Contact_01), J901.1 (Contact_01)
/TI_TARGET_RESET_N: J900.11 (Contact_11)
/TI_UART_A_RX: J901.19 (Contact_19)
/TI_UART_A_TX: J901.18 (Contact_18)
/TI_UART_B_RX: J901.22 (Contact_22)
/TI_UART_B_TX: J901.21 (Contact_21)
GND: EXT1.22, EXT2.1, EXT2.21, EXT2.22, U$1.GND

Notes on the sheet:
*NC
+3.3V at Iout(max)=600mA, Power Out!
+5V Only!!! Power In/Out

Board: 2 copper layers, 5 parts (0 on the bottom side), 5 nets, no tracks yet.
